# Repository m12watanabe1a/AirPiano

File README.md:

# AirPiano

Hptics Device PCB with ESP32

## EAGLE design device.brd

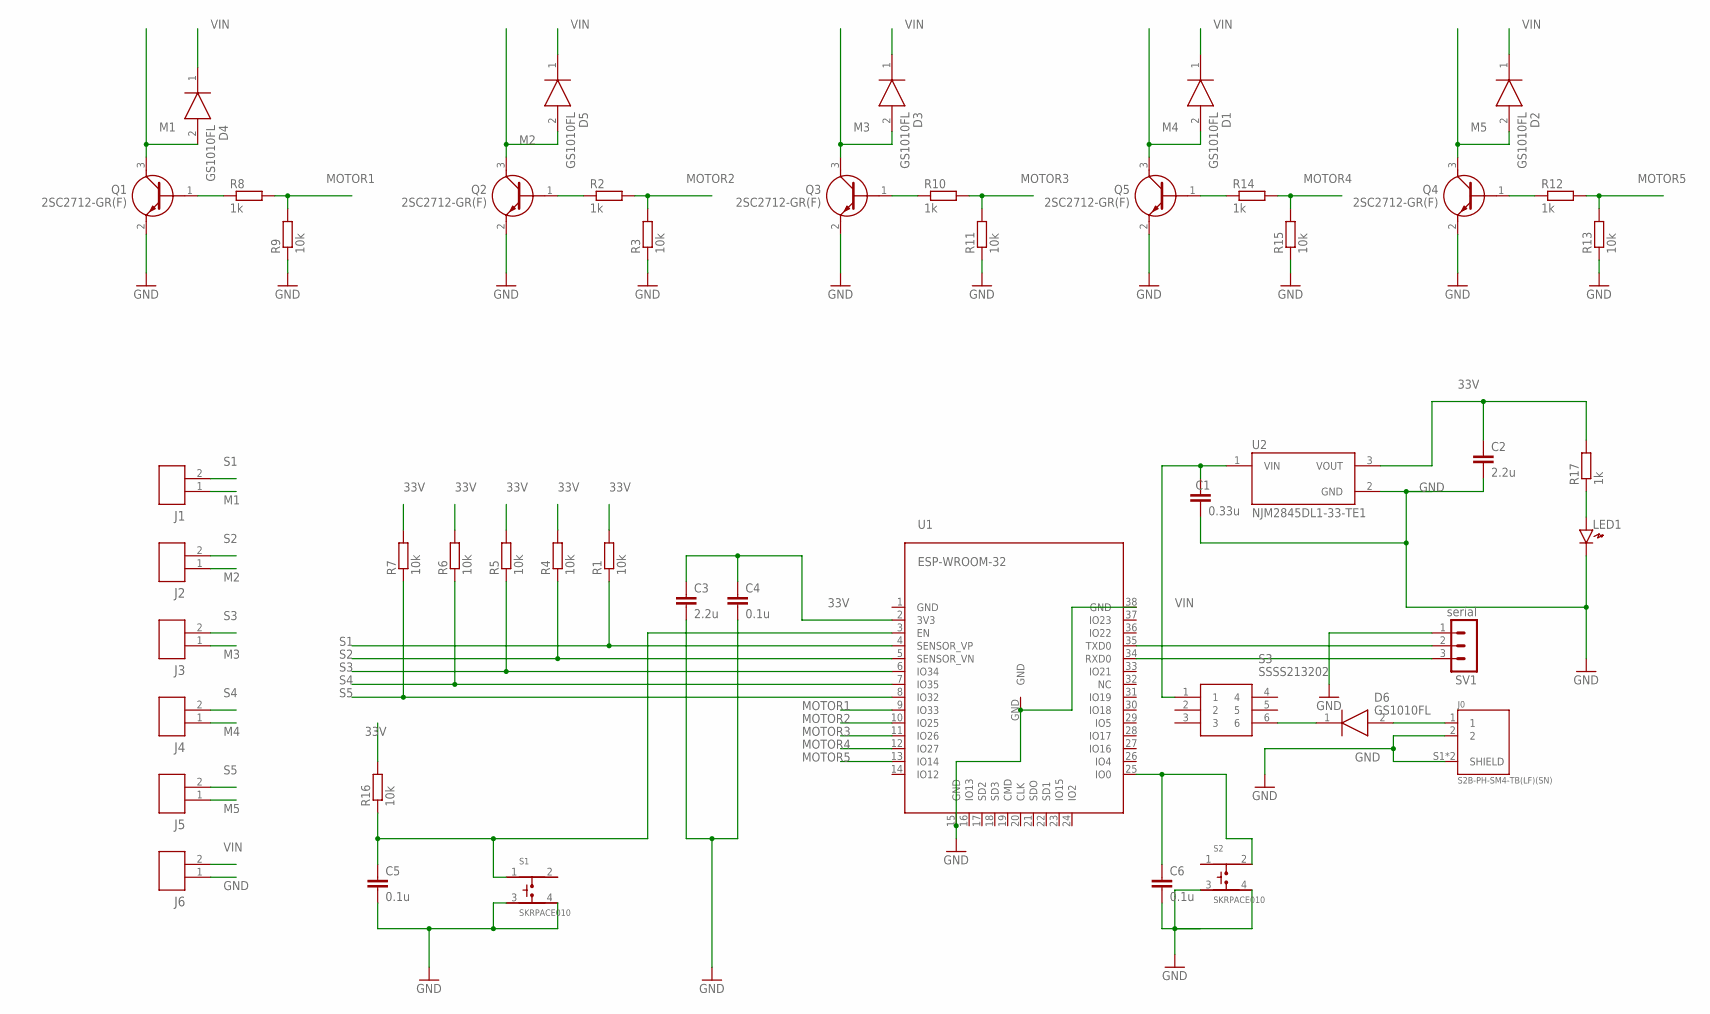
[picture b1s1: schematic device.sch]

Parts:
C1: 0.33u; C025-024X044
C2, C3: 2.2u; C0402
C4, C5, C6: 0.1u; C0402
D1, D2, D3, D4, D5, D6: GS1010FL; SODFL3618X110N
J0: S2B-PH-SM4-TB(LF)(SN); JST_S2B-PH-SM4-TB(LF)(SN)
J1, J2, J3, J4, J5, J6: JST_ZH_2PIN
LED1: LED1608
Q1, Q2, Q3, Q4, Q5: 2SC2712-GR(F); SC-59
R1, R3, R4, R5, R6, R7, R9, R11, R13, R15, R16: 10k; R0603
R2, R8, R10, R12, R14, R17: 1k; R0603
S1, S2: SKRPACE010; SW_SKRPACE010
S3: SSSS213202
SV1: serial; MA03-1
U1: ESP-WROOM-32
U2: NJM2845DL1-33-TE1; DPAK228P968X238-4N

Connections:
33V: C2.1, C3.1, C4.1, R1.2, R4.2, R5.2, R6.2, R7.2, R16.2, R17.2, U1.2 (3V3), U2.3 (VOUT)
GND: C1.2, C2.2, C3.2, C4.2, C5.2, C6.2, J0.2, J0.S1 (SHIELD), J0.S2 (SHIELD), J6.1, LED1.K, Q1.2 (E), Q2.2 (E), Q3.2 (E), Q4.2 (E), Q5.2 (E), R3.1, R9.1, R11.1, R13.1, R15.1, S1.3, S1.4, S2.3, S2.4, SV1.1, U1.15 (GND), U1.38 (GND), U1.GND, U2.2 (GND)
M1: D4.2 (A), J1.1, Q1.3 (C)
M2: D5.2 (A), J2.1, Q2.3 (C)
M3: D3.2 (A), J3.1, Q3.3 (C)
M4: D1.2 (A), J4.1, Q5.3 (C)
M5: D2.2 (A), J5.1, Q4.3 (C)
MOTOR1: R8.2, R9.2, U1.9 (IO33)
MOTOR2: R2.2, R3.2, U1.10 (IO25)
MOTOR3: R10.2, R11.2, U1.11 (IO26)
MOTOR4: R14.2, R15.2, U1.12 (IO27)
MOTOR5: R12.2, R13.2, U1.13 (IO14)
unnamed: C5.1, R16.1, S1.1, U1.3 (EN)
unnamed: Q2.1 (B), R2.1
unnamed: C6.1, S2.2, U1.25 (IO0)
unnamed: SV1.2, U1.35 (TXD0)
unnamed: SV1.3, U1.34 (RXD0)
unnamed: Q3.1 (B), R10.1
unnamed: LED1.A, R17.1
unnamed: D6.1 (K), S3.6
unnamed: Q1.1 (B), R8.1
unnamed: Q4.1 (B), R12.1
unnamed: Q5.1 (B), R14.1
unnamed: D6.2 (A), J0.1
S1: J1.2, R1.1, U1.4 (SENSOR_VP)
S2: J2.2, R4.1, U1.5 (SENSOR_VN)
S3: J3.2, R5.1, U1.6 (IO34)
S4: J4.2, R6.1, U1.7 (IO35)
S5: J5.2, R7.1, U1.8 (IO32)
VIN: C1.1, D1.1 (K), D2.1 (K), D3.1 (K), D4.1 (K), D5.1 (K), J6.2, S3.1, U2.1 (VIN)

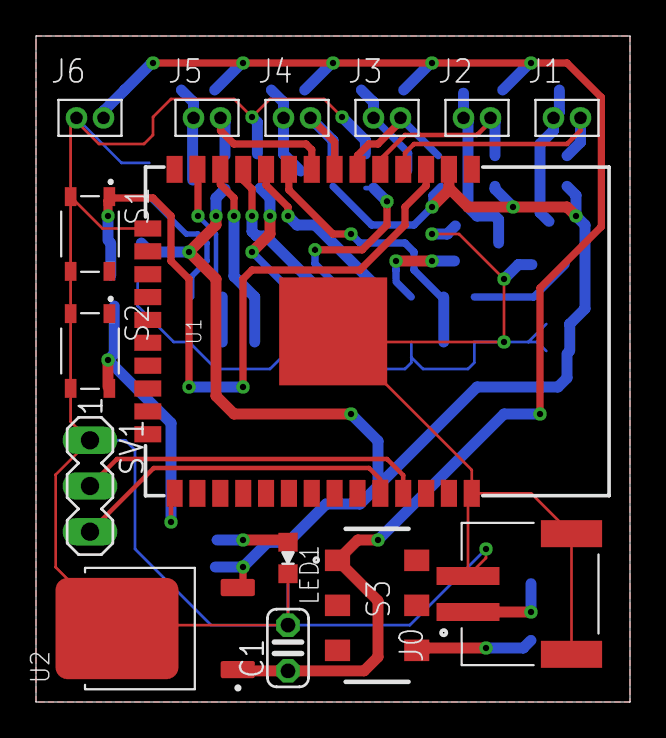
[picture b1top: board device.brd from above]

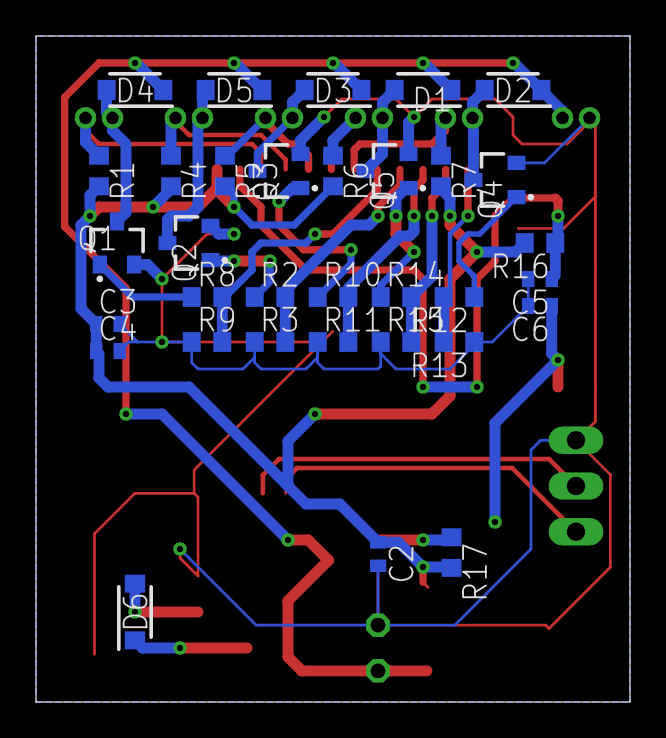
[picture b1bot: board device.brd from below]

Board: 2 copper layers, 33.0 x 37.0 mm, 48 parts (33 on the bottom side), 30 nets.

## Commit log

2019-09-17 circuit completed
2019-09-29 exchange VCC and GND
2019-10-01 fix images
2019-10-08 Manual routing of V2.0.0
2019-10-08 Modifie board
2019-10-08 update circuit and images
2019-10-08 update files
